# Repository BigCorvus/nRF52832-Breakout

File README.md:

# nRF52832-Breakout
breakout board for the CDSENET E73-2G4M04S1B module

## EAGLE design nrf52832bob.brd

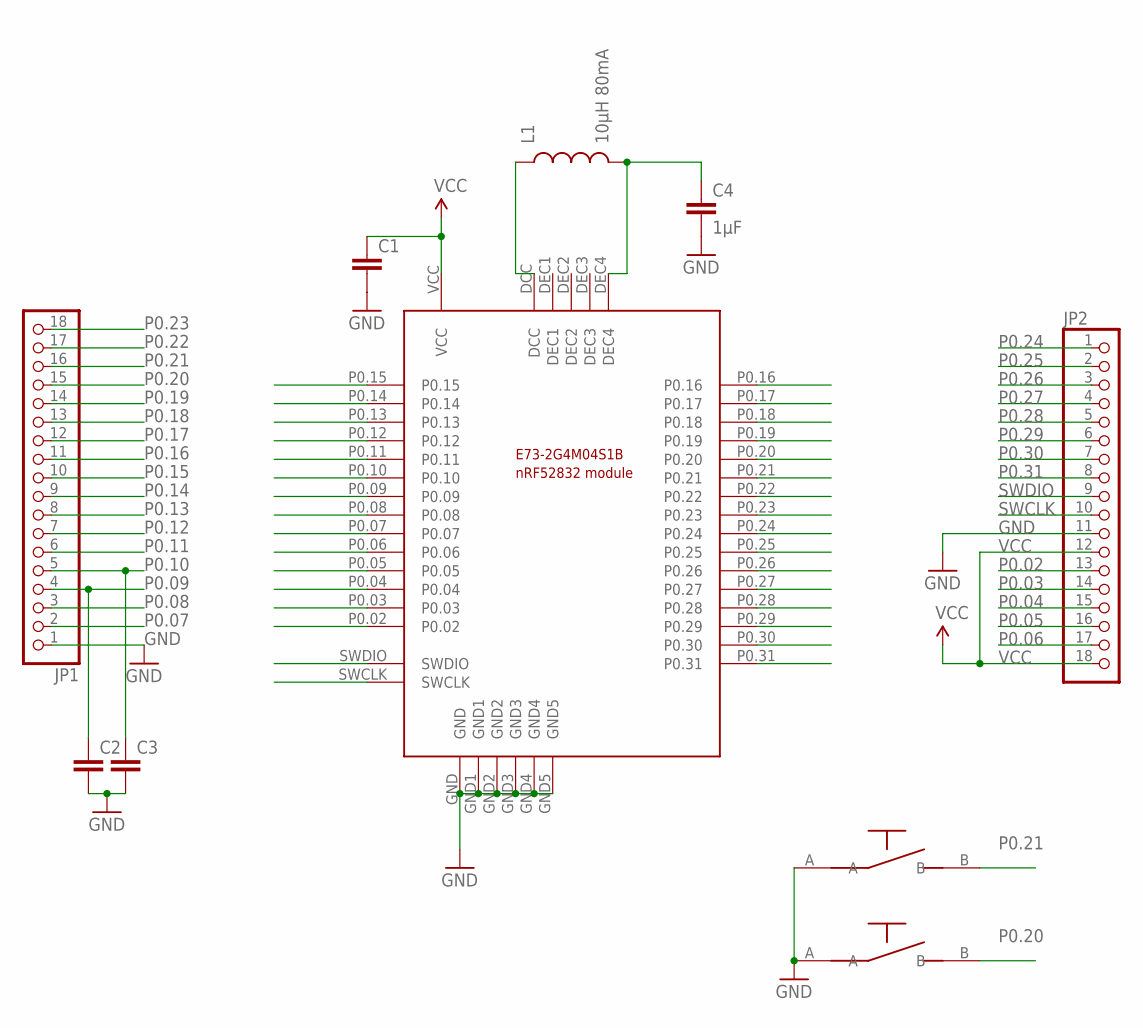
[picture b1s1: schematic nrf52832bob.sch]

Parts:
C1: C-EUC0805; C0805
C2, C3: C-EUC0603; C0603
C4: 1µF; C0603
JP1, JP2: PINHD-1X18-BIG; 1X18-BIG
L1: 10µH 80mA; 0603
U$1: NRF52832MODULE
U$2, U$3: SWITCH2PIN

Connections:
GND: C1.2, C2.2, C3.2, C4.2, JP1.1, JP2.11, U$1.GND, U$1.GND1, U$1.GND2, U$1.GND3, U$1.GND4, U$1.GND5, U$2.A, U$3.A
unnamed: L1.1, U$1.DCC
unnamed: C4.1, L1.2, U$1.DEC4
P0.02: JP2.13, U$1.P0.02
P0.03: JP2.14, U$1.P0.03
P0.04: JP2.15, U$1.P0.04
P0.05: JP2.16, U$1.P0.05
P0.06: JP2.17, U$1.P0.06
P0.07: JP1.2, U$1.P0.07
P0.08: JP1.3, U$1.P0.08
P0.09: C2.1, JP1.4, U$1.P0.09
P0.10: C3.1, JP1.5, U$1.P0.10
P0.11: JP1.6, U$1.P0.11
P0.12: JP1.7, U$1.P0.12
P0.13: JP1.8, U$1.P0.13
P0.14: JP1.9, U$1.P0.14
P0.15: JP1.10, U$1.P0.15
P0.16: JP1.11, U$1.P0.16
P0.17: JP1.12, U$1.P0.17
P0.18: JP1.13, U$1.P0.18
P0.19: JP1.14, U$1.P0.19
P0.20: JP1.15, U$1.P0.20, U$3.B
P0.21: JP1.16, U$1.P0.21, U$2.B
P0.22: JP1.17, U$1.P0.22
P0.23: JP1.18, U$1.P0.23
P0.24: JP2.1, U$1.P0.24
P0.25: JP2.2, U$1.P0.25
P0.26: JP2.3, U$1.P0.26
P0.27: JP2.4, U$1.P0.27
P0.28: JP2.5, U$1.P0.28
P0.29: JP2.6, U$1.P0.29
P0.30: JP2.7, U$1.P0.30
P0.31: JP2.8, U$1.P0.31
SWCLK: JP2.10, U$1.SWCLK
SWDIO: JP2.9, U$1.SWDIO
VCC: C1.1, JP2.12, JP2.18, U$1.VCC

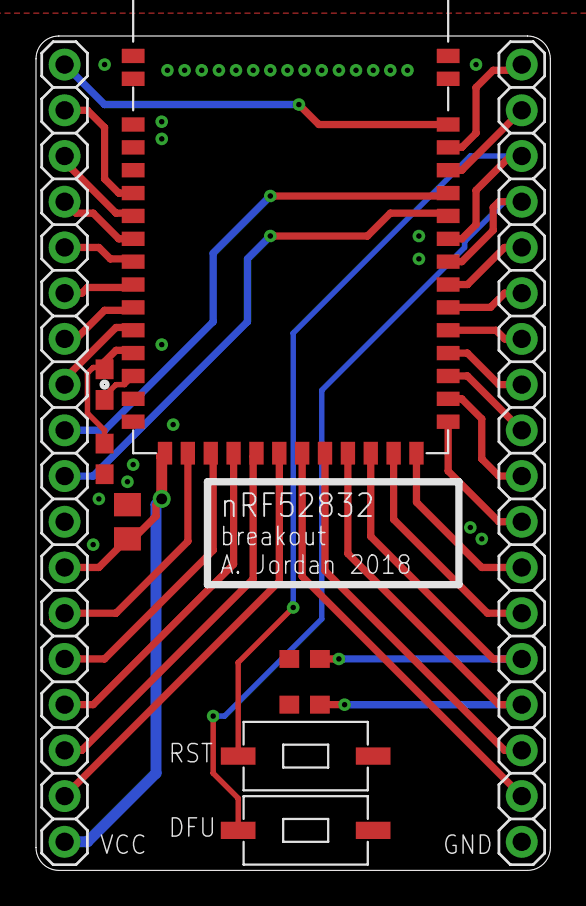
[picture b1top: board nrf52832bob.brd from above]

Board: 2 copper layers, 28.6 x 46.4 mm, 10 parts (0 on the bottom side), 36 nets.

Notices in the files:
parts and their libraries:
SparkFun-Passives: Licensing: Creative Commons ShareAlike 4.0 International - https://creativecommons.org/licenses/by-sa/4.0
